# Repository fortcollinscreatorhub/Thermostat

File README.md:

# What is this repository?

This repository contains files for the custom thermostats used at the Fort
Collins Creator Hub.

# How to clone this repository

This project uses git submodules, unfortunately. To clone the repository, run:

```shell
git clone --recurse-submodules https://github.com/fortcollinscreatorhub/Thermostat
```

If you wish to push back to the github repo, you probably want to clone with
`ssh`, or edit `.git/config` to use ssh URLs after cloning, e.g.:

```shell
git clone --recurse-submodules git@github.com:fortcollinscreatorhub/Thermostat
```

Or after cloning:

```shell
vi .git/config
```

Even if you clone using the ssh URL, you'll still need to edit the remote
definition for each submodule after the initial clone operation.

## Hardware Revisions

v1 was a a breadboard-based design, using some standalone (non-WiFi)
micro-controller; perhaps an AVR or STM32. For this design, we only have the
software and not schematics etc.

v2 uses an ESP32. The PCB design is found in directory [pcb/](pcb/). File
[thermostat.dxf](thermostat.dxf) describes some of the physical design.

## Software Versions

v1 hardware uses the code in directory [code/arduino-v1/](code/arduino-v1/).

v2 hardware can use any of following software stacks:
* A port of the older Arduino code. Found in directory
[code/arduino-esp32/](code/arduino-esp32/).
* WiFi-/MQTT-capable software built using the ESP-IDF framework. Found in
directory [code/esp-idf](code/esp-idf). This version is currently deployed.
* Updated WiFi-/MQTT-capable software built using the ESP-IDF framework, plus
the FCCH "connection manager" component which provides a permanently enabled
password-protected web admin interface. Found in directory
[code/esp-idf-v2](code/esp-idf-v2). This version is not yet deployed.

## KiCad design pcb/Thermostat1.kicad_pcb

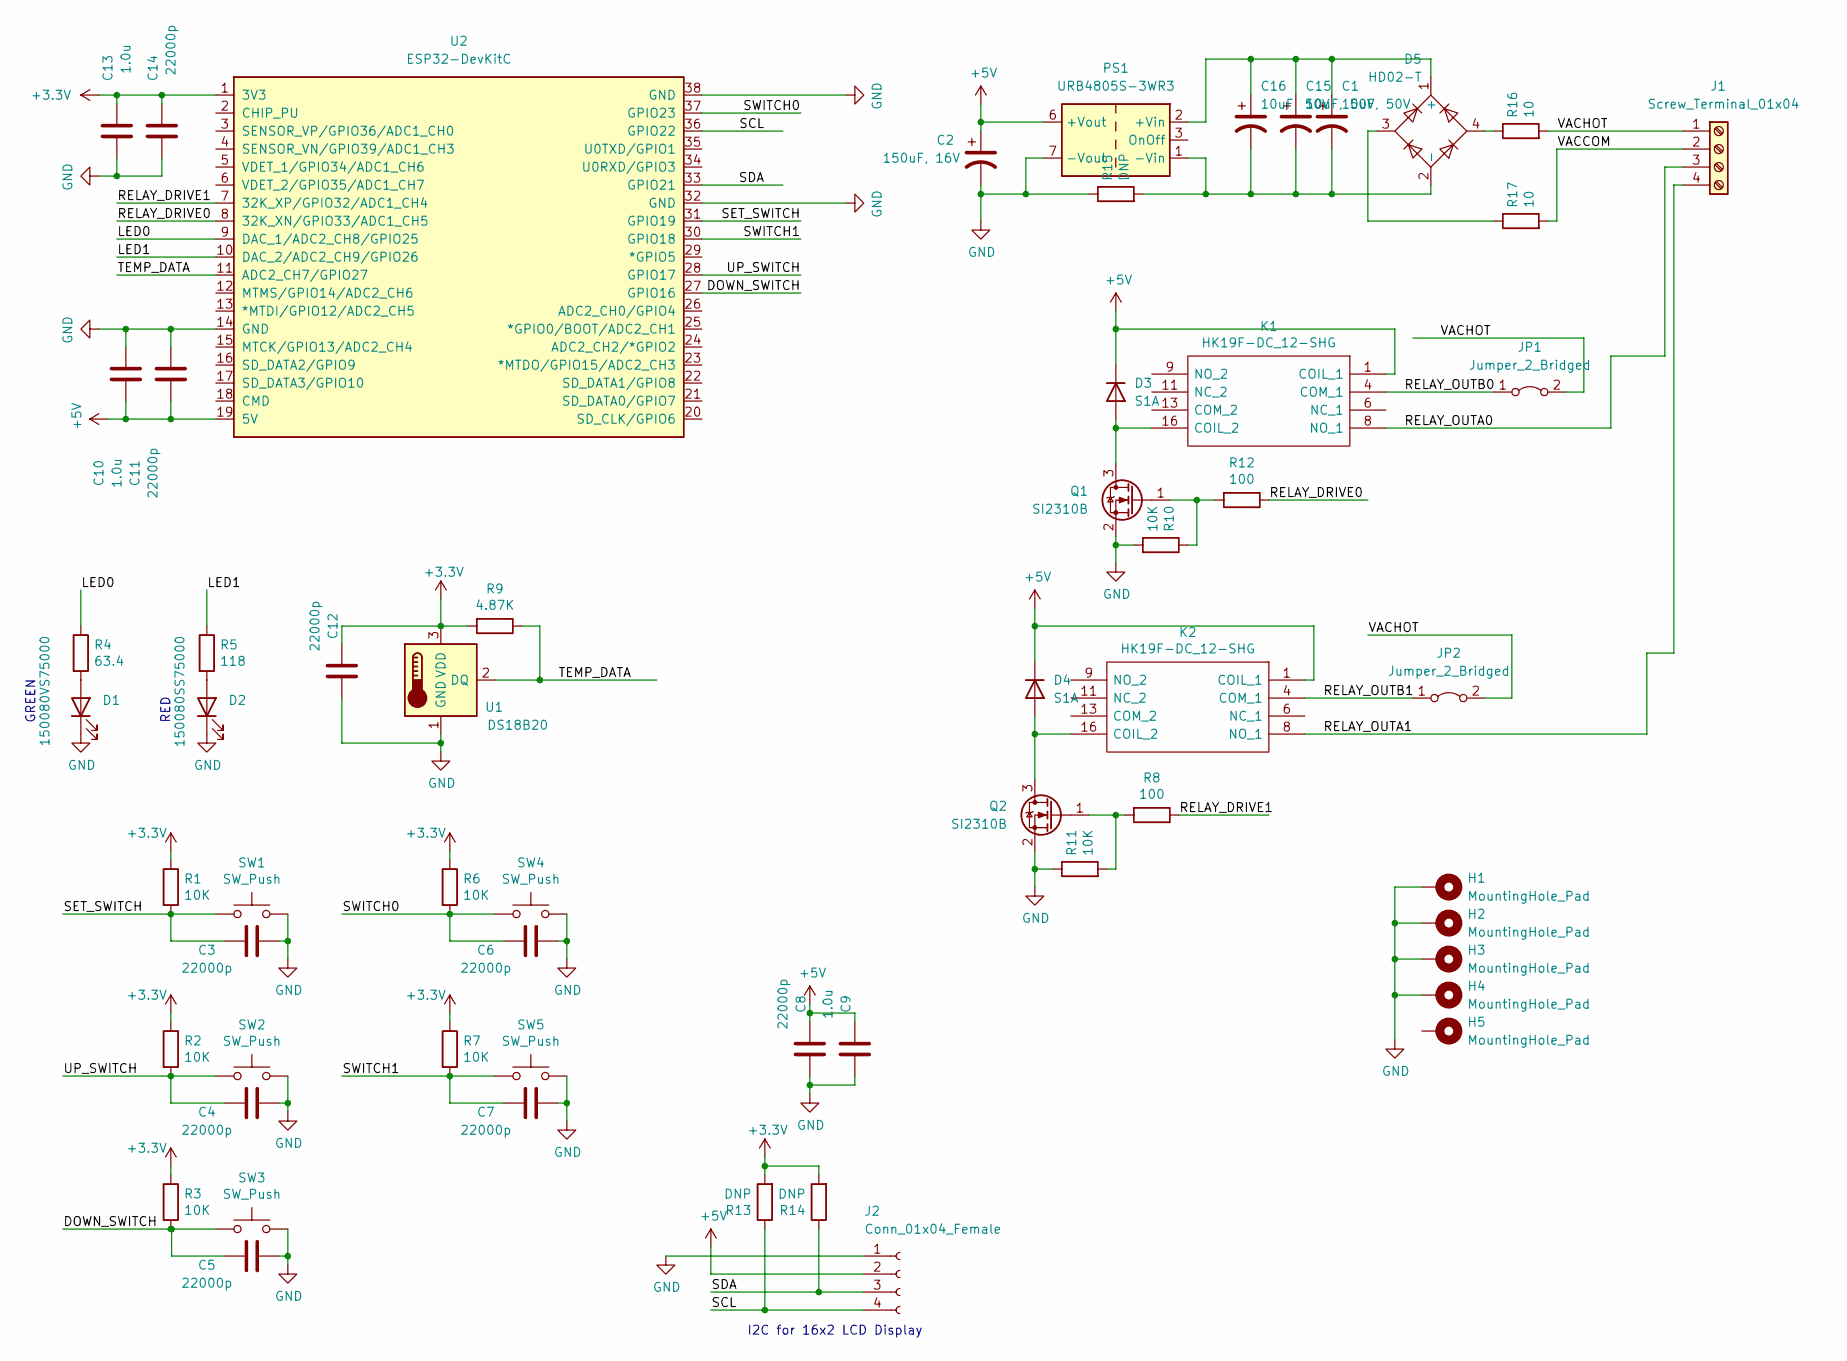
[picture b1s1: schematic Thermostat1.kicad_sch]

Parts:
C1: 10uF, 50V; CP_EIA-7343-43_Kemet-X_Pad2.25x2.55mm_HandSolder
C2: 150uF, 16V; CP_EIA-7343-43_Kemet-X_Pad2.25x2.55mm_HandSolder
C3, C4, C5, C6, C7, C8, C11, C12, C14: 22000p; C_0603_1608Metric_Pad1.08x0.95mm_HandSolder
C9, C10, C13: 1.0u; C_0805_2012Metric_Pad1.18x1.45mm_HandSolder
C15: 10uF, 50V; CP_Radial_D5.0mm_P2.00mm
C16: 10uF, 50V; CP_Radial_D8.0mm_P5.00mm
D1: 150080VS75000; LED_0603_1608Metric_Pad1.05x0.95mm_HandSolder
D2: 150080SS75000; LED_0603_1608Metric_Pad1.05x0.95mm_HandSolder
D3, D4: S1A; D_SMA
D5: HD02-T; SO-4_4.4x3.9mm_P2.54mm
H1, H2, H3, H4, H5: MountingHole_Pad; MountingHole_3.2mm_M3_DIN965_Pad
J1: Screw_Terminal_01x04; TerminalBlock_Altech_AK300-4_P5.00mm
J2: Conn_01x04_Female; PinHeader_1x04_P2.54mm_Vertical
JP1, JP2: Jumper_2_Bridged; PinHeader_1x02_P2.54mm_Vertical
K1, K2: HK19F-DC_12-SHG; Relay_DPDT_Omron_G5V-2; Manufacturer_Part_Number HK19F-DC 12-SHG
PS1: URB4805S-3WR3; Converter_DCDC_XP_POWER-ITxxxxxS_THT
Q1, Q2: SI2310B; SOT-23
R1, R2, R3, R6, R7, R10, R11: 10K; R_0603_1608Metric_Pad0.98x0.95mm_HandSolder
R4: 63.4; R_1206_3216Metric_Pad1.30x1.75mm_HandSolder
R5: 118; R_1206_3216Metric_Pad1.30x1.75mm_HandSolder
R8, R12: 100; R_0603_1608Metric_Pad0.98x0.95mm_HandSolder
R9: 4.87K; R_0603_1608Metric_Pad0.98x0.95mm_HandSolder
R13, R14: DNP; R_0603_1608Metric_Pad0.98x0.95mm_HandSolder
R15: DNP; R_1206_3216Metric_Pad1.30x1.75mm_HandSolder
R16, R17: 10; R_1206_3216Metric_Pad1.30x1.75mm_HandSolder
SW1, SW2, SW3: SW_Push; SW_PUSH_6mm
SW4, SW5: SW_Push; SW_PUSH-12mm
U1: DS18B20; TO-92_Inline_Wide
U2: ESP32-DevKitC

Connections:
+3.3V: C12.1, C13.1, C14.1, R1.1, R2.1, R3.1, R6.1, R7.1, R9.2, R13.2, R14.2, U1.3 (VDD), U2.1 (3V3)
+5V: C2.1, C8.1, C9.1, C10.2, C11.2, D3.1 (K), D4.1 (K), J2.2, K1.1 (COIL_1), K2.1 (COIL_1), PS1.6 (+Vout), U2.19 (5V)
/DOWN_SWITCH: C5.1, R3.2, SW3.1, U2.27 (GPIO16)
/LED0: R4.1, U2.9 (DAC_1/ADC2_CH8/GPIO25)
/LED1: R5.1, U2.10 (DAC_2/ADC2_CH9/GPIO26)
/RELAY_DRIVE0: R12.1, U2.8 (32K_XN/GPIO33/ADC1_CH5)
/RELAY_DRIVE1: R8.1, U2.7 (32K_XP/GPIO32/ADC1_CH4)
/RELAY_OUTA0: J1.3, K1.8 (NO_1)
/RELAY_OUTA1: J1.4, K2.8 (NO_1)
/RELAY_OUTB0: JP1.1 (A), K1.4 (COM_1)
/RELAY_OUTB1: JP2.1 (A), K2.4 (COM_1)
/SCL: J2.4, R13.1, U2.36 (GPIO22)
/SDA: J2.3, R14.1, U2.33 (GPIO21)
/SET_SWITCH: C3.1, R1.2, SW1.1, U2.31 (GPIO19)
/SWITCH0: C6.1, R6.2, SW4.1, U2.37 (GPIO23)
/SWITCH1: C7.1, R7.2, SW5.1, U2.30 (GPIO18)
/TEMP_DATA: R9.1, U1.2 (DQ), U2.11 (ADC2_CH7/GPIO27)
/UP_SWITCH: C4.1, R2.2, SW2.1, U2.28 (GPIO17)
/VACCOM: J1.2, R17.2
/VACHOT: J1.1, JP1.2 (B), JP2.2 (B), R16.2
GND: C2.2, C3.2, C4.2, C5.2, C6.2, C7.2, C8.2, C9.2, C10.1, C11.1, C12.2, C13.2, C14.2, D1.1 (K), D2.1 (K), H1.1, H2.1, H3.1, H4.1, J2.1, PS1.7 (-Vout), Q1.2 (S), Q2.2 (S), R10.2, R11.1, R15.1, SW1.2, SW2.2, SW3.2, SW4.2, SW5.2, U1.1 (GND), U2.14 (GND), U2.32 (GND), U2.38 (GND)
unnamed: C1.1, C15.1, C16.1, D5.1 (+), PS1.2 (+Vin)
unnamed: C1.2, C15.2, C16.2, D5.2 (-), PS1.1 (-Vin), R15.2
unnamed: D1.2 (A), R4.2
unnamed: D2.2 (A), R5.2
unnamed: D3.2 (A), K1.16 (COIL_2), Q1.3 (D)
unnamed: D4.2 (A), K2.16 (COIL_2), Q2.3 (D)
unnamed: D5.3, R17.1
unnamed: D5.4, R16.1
unnamed: Q1.1 (G), R10.1, R12.2
unnamed: Q2.1 (G), R8.2, R11.2

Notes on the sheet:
I2C for 16x2 LCD Display
RED
GREEN

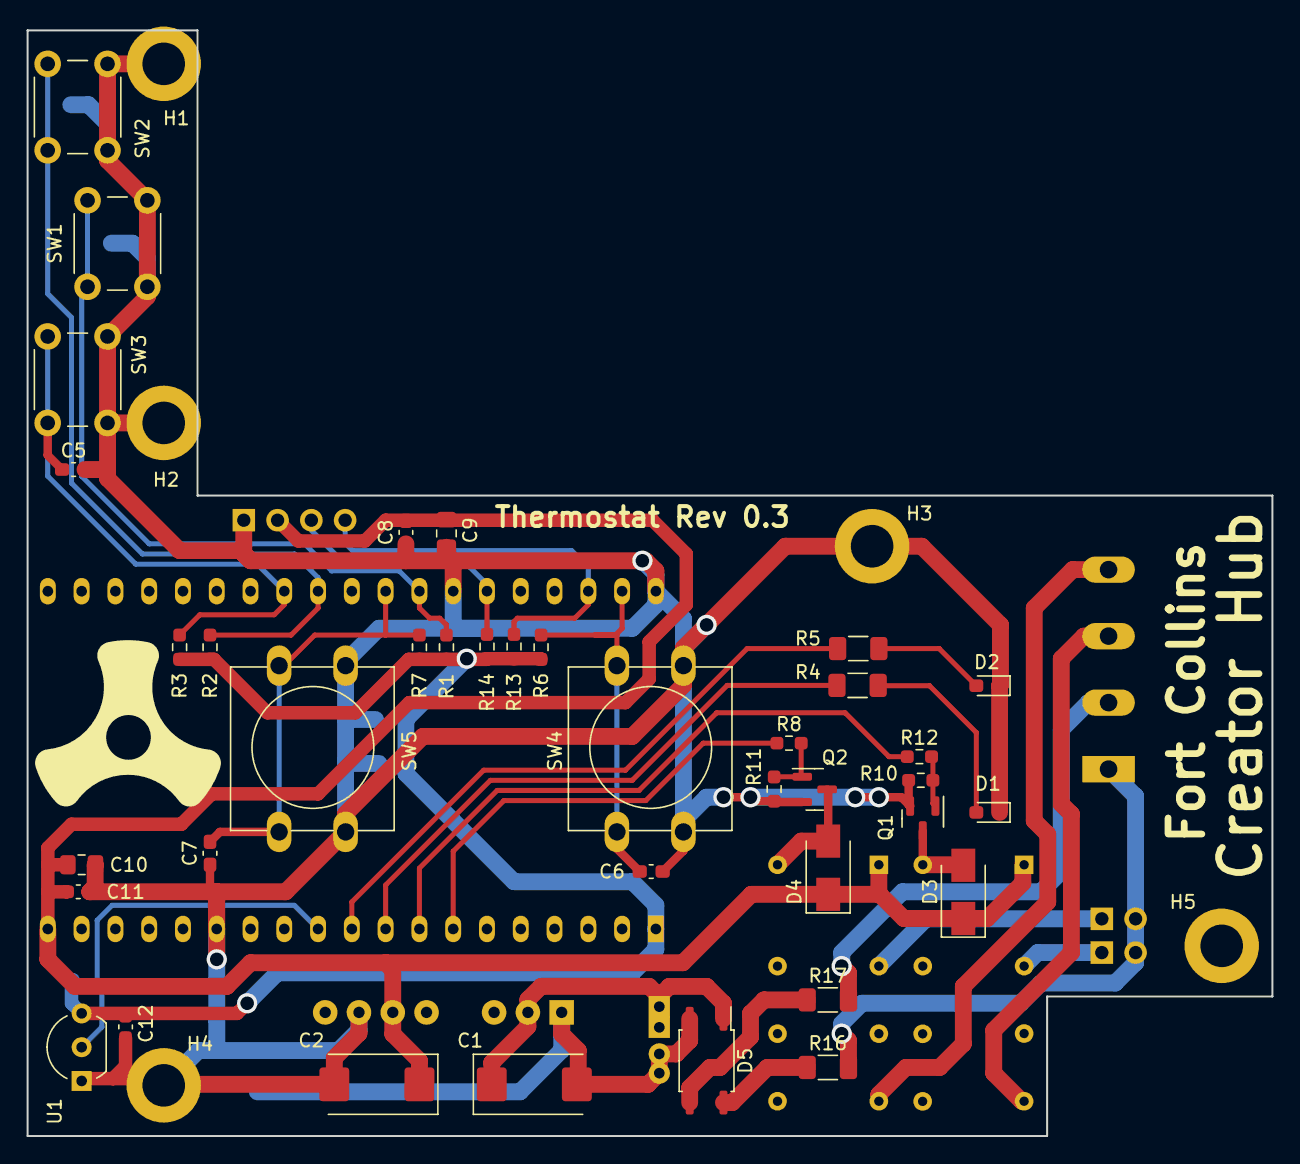
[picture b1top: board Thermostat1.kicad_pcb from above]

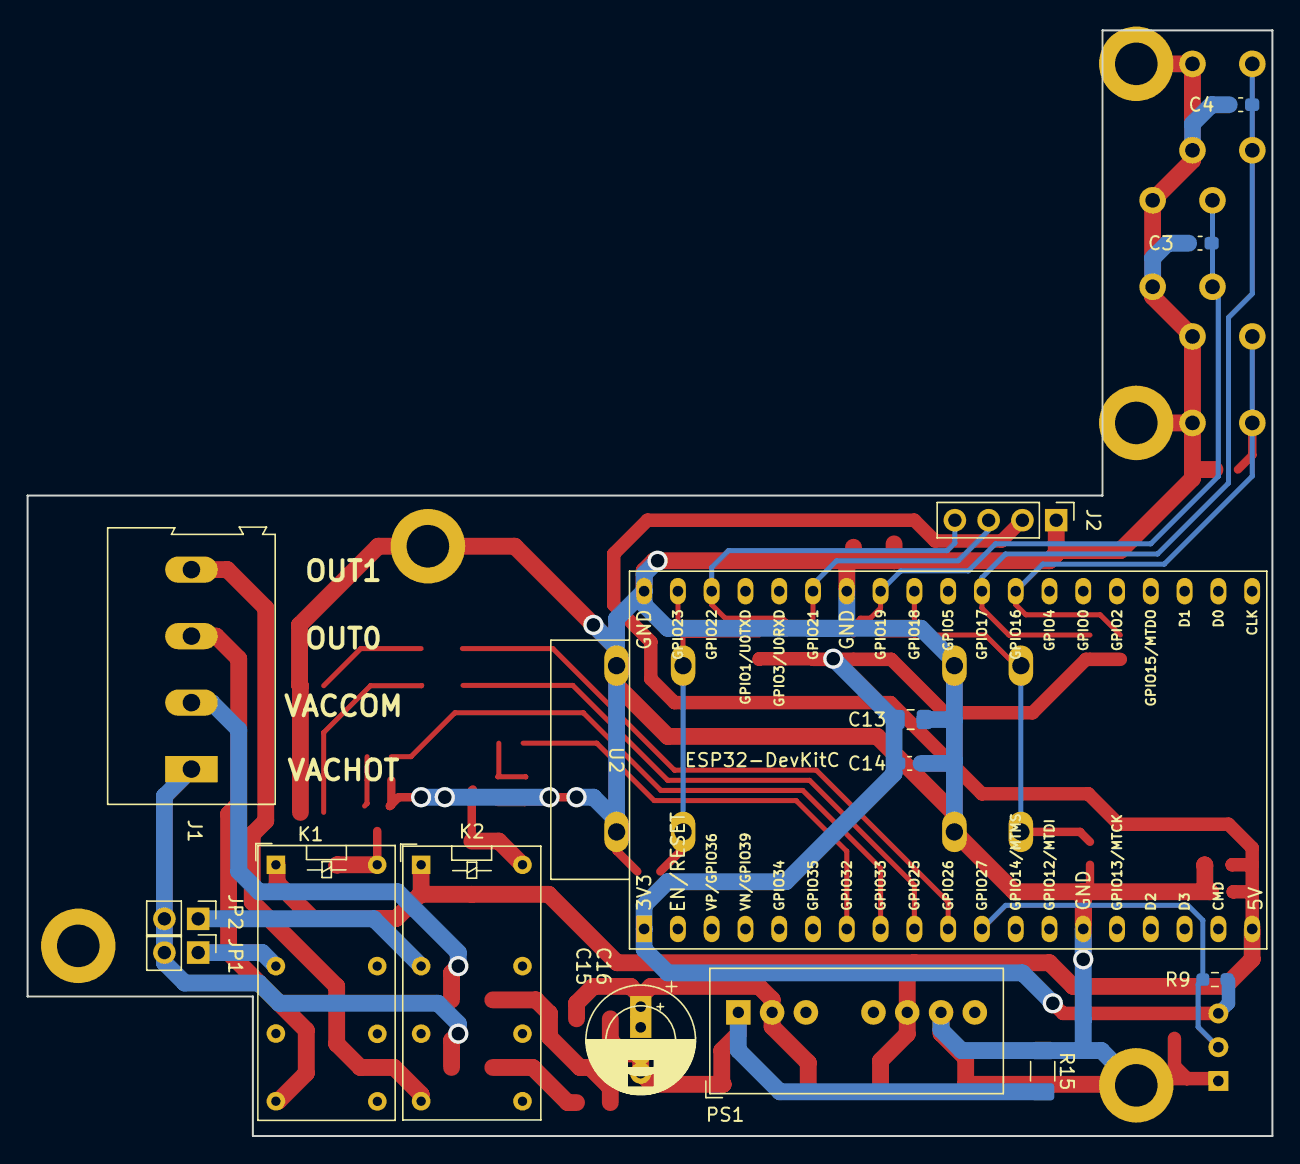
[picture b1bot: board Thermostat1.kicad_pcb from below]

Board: 2 copper layers, 93.6 x 83.1 mm, 59 parts (16 on the bottom side), 31 nets.

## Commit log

2022-11-16 Added KiCad PCB files.
2022-11-16 Added dxf sketch of thermostat repackage along with some datasheets for parts to use.
2022-12-10 New revision of pcb with updates suggested by Steve P.
2022-12-10 Removed some files which don't appear to be used anymore by newer version of KiCad.
2022-12-11 Fixed a couple issues on schematic and layout - swapped power supplies on external components and pullups from 5V to 3.3V, moved input connector so it's further from the edge of the box, increased sp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
2022-12-13 A few more fixes for Rev 0.3 - more options for power input caps as well as some sense resistors, also remade gerber files.
2022-12-13 Added new zip archive of fab files for Rev. 0.3
2022-12-20 Imported new pcb layout into mechanical DXF, added 'vent' hole for thermometer part.
2022-12-21 Create LICENSE
2023-01-17 Added callouts for lightpipes and button key caps.
2023-01-24 Adding ESP32 versions
    Adding ESP32 versions
2023-02-06 Update main.c
    Updated temperature read
2023-02-13 Renamed src directory to main.
2023-02-13 Updated src directory reference to main.
2024-04-25 Add docs & script to build with ESP-IDF Docker
2025-02-21 Re-org directory layout
    Add a little more structure and documentation.
2025-03-14 code: copy utilities from rfid-v2
    * tasks.json to allow building etc. from vscode.
    * build.sh fix to allow serial port to work inside Docker.
2025-03-26 esp-idf-v2: add skeleton app
    This software version will use the recently-written "FCCH connection
    manager" component for WiFi and other configuration. This commit adds an
    extremely bare skeleton; just enough to build an empty application binary.
2025-03-26 esp-idf-v2: connmgr: enhance style test
    Adapt the style test HTML file to better match the content that the code
    generates.
2025-03-26 esp-idf-v2: components: esp32-i2c-lcd1602: port to ESP-IDF v5.4
2025-03-26 esp-idf-v2: connmgr: add application version logic
2025-03-26 esp-idf-v2: components: add fcch_connmgr
    This code was taken from https://github.com/fortcollinscreatorhub/rfid-v2
    commit 54737a166ac68ece5f1060d2a6bf5534e063a4dd directory
    components/fcch_connmgr. Eventually we will transform it into a git
    submodule so updates can be more easily shared between projects, but for
    now simply copying it is easiest.
2025-03-26 esp-idf-v2: components: add esp32-i2c-lcd1602
    git clone https://github.com/DavidAntliff/esp32-i2c-lcd1602.git
    (This yielded commit c9026dd74f63e64943321a4dea5f4ce9f8d9e9c5)
    rm -rf esp32-i2c-lcd1602/.git/
    git add esp32-i2c-lcd1602
2025-03-26 esp-idf-v2: components: esp32-smbus: port to ESP-IDF v5.4
2025-03-26 esp-idf-v2: components: add esp32-smbus
    git clone https://github.com/DavidAntliff/esp32-smbus.git
    (This yielded commit 1bca026c4fe8d28f9cb76da30da05e8a70a8231f)
    rm -rf esp32-smbus/.git/
    git add esp32-smbus
2025-03-26 esp-idf-v2: full application implementation
2025-03-28 esp-idf-v2: quantize temps in MQTT msgs
    Format temperatures to 1 decimal place in MQTT messages. This matches
    the LCD display, and produces "simpler" values in messages, and Node-RED
    status displays.
2025-03-31 fcch_connmgr: convert to git submodule
2025-04-02 fcch_connmgr: switch to latest version
    This version brings support for CM_CONF_ITEM_TYPE_FLOAT, which the
    thermostat app will use in the next commit.
2025-04-02 Convert config items to floats
    This allows finer-grained control, and support for signed values, which
    is useful for the sensor offset value.
2025-04-02 Add HTTP buttons for start/cancel override
2025-04-02 Add HTTP button to force heating on for testing
2025-05-24 add shim design for probe mounting tube
    Sometimes the right-angle PVC joint doesn't push all the way onto the
    PVC extending from the box. This shim can be placed around the piece
    that extends from the box between the box and the right-angle piece to
    square everything up.
